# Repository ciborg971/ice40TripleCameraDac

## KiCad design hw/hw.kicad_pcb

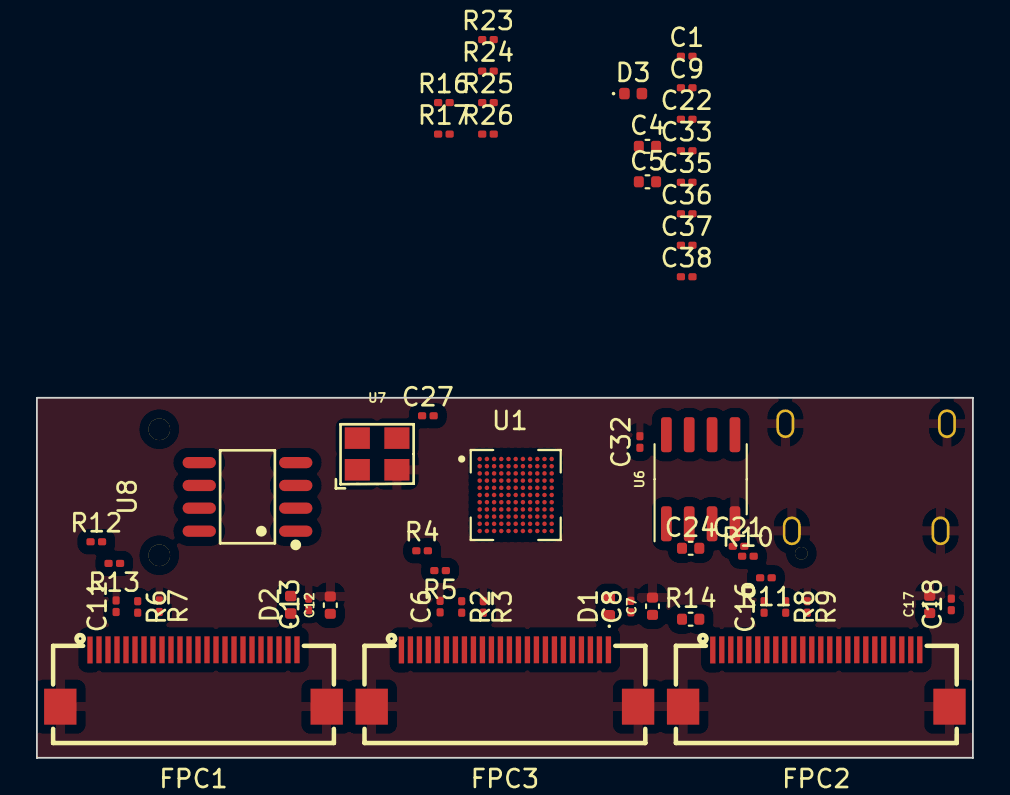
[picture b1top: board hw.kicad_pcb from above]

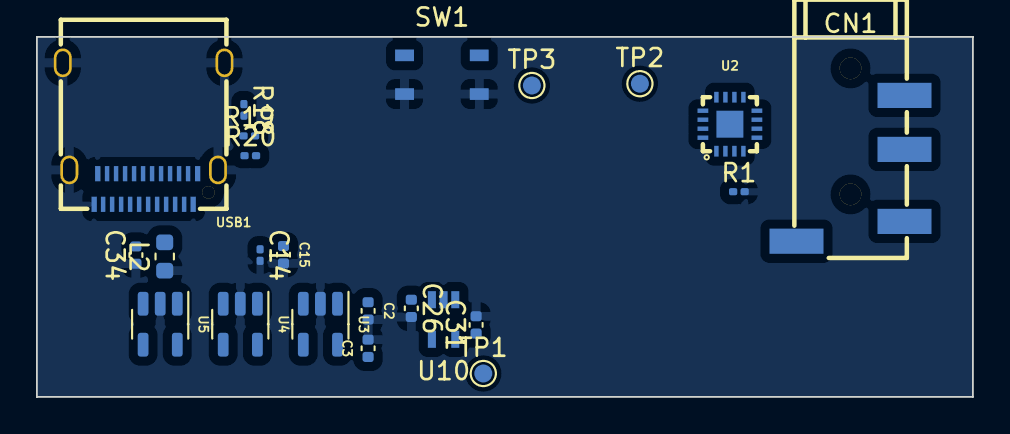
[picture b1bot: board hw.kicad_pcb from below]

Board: 2 copper layers, 52.0 x 20.0 mm, 75 parts (23 on the bottom side), 76 nets, no tracks yet.

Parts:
C1, C6, C8, C9, C11, C13, C14, C16, C18, C21, C22, C27, C32, C38: 100nF; C_0201_0603Metric
C2, C3, C4, C5: 22uF; C_0402_1005Metric
C7, C12, C17: 2.2uF; C_0402_1005Metric
C15: 4.7uF; C_0402_1005Metric
C24, C34: 10uF; C_0402_1005Metric
C26, C31: 1uF; C_0402_1005Metric
C33, C35, C36, C37: 10nF; C_0201_0603Metric
CN1: PJ-320D; AUDIO-SMD_PJ-320D
D1, D2, D3: D; D_0402_1005Metric
FPC1, FPC2, FPC3: AFC24-S24FIC-00; FPC-SMD_P0.50-24P_QCHF-SM-H2.0
L2: Bead; L_0603_1608Metric
R1, R16: 5.1K; R_0201_0603Metric
R2, R3, R6, R7, R8, R9: 10K; R_0201_0603Metric
R4, R5, R10, R11, R12, R13: 4.7K; R_0201_0603Metric
R14: 0R; C_0402_1005Metric
R17: 100; R_0201_0603Metric
R18: 1.5k; R_0201_0603Metric
R19, R20: 68; R_0201_0603Metric
R23, R24, R26: 10k; R_0201_0603Metric
R25: R; R_0201_0603Metric
SW1: SW_Push; PTS_810_SMT_Switch
TP1, TP2, TP3: TEST; TestPoint_Pad_D1.0mm
U1: ICE40LP8K-CM121; BGA121N40P11X11_500X500X100N
U2: MAX98357AETE+T; TQFN-16_L3.0-W3.0-P0.50-BL-EP1.5
U3: AP2112K-3.3; SOT-23-5
U4: AP2112K-1.8; SOT-23-5
U5: MIC5219-2.8YM5; SOT-23-5
U6: AT25SF081-SSHD-X; SOIC-8_3.9x4.9mm_P1.27mm
U7: YF4016M00033T8188092; OSC-SMD_4P-L3.2-W2.5-BL
U8: PM004MNIATR; SOP-8_L4.9-W3.9-P1.27-LS6.0-BL
U10: MIC5365-1.2YC5-TR; SC-70-C5
USB1: 12401832E402A; USB-C-TH_12401832E402A

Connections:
82: R23.2, TP2.1, U1.K6 (IOB_82_GBIN4), U6.3 (~WP/IO2)
109: R24.2, U1.H10 (IOR_116), U6.7 (~HOLD/IO3)
+1V2: C22.1, C31.1, C33.1, C35.1, R17.2, TP1.1, U1.D4 (VCC), U1.D8 (VCC__1), U1.G1 (IOL_14A_GBIN6), U1.H4 (VCC__2), U1.H8 (VCC__3), U10.5 (VOUT)
+1V8: FPC1.10, FPC2.10, FPC3.10, U4.5 (VOUT)
+2V8: D1.2 (A), D2.2 (A), D3.2 (A), FPC1.11, FPC2.11, FPC3.11, R4.2, R5.2, R10.2, R11.2, R12.2, R13.2, U5.5 (OUT)
+3.3V: C1.1, C3.1, C9.1, C14.1, C15.1, C36.1, C37.1, C38.1, R2.1, R6.1, R8.1, R23.1, R24.1, U3.5 (VOUT), U6.8 (VCC)
+3V3: C21.1, C26.1, C32.1, R14.1, R25.1, R26.1, U1.B8 (IOT_177), U1.C10 (VPP_2V5), U1.D6 (VCCIO_0), U1.E4 (VCCIO_3), U1.F8 (VCCIO_1), U1.G4 (VCCIO_3__1), U1.G10 (IOR_120), U1.H6 (VCCIO_2), U1.L11 (VCC_SPI), U7.4 (Vdd), U10.1 (VIN), U10.3 (EN)
/AVCC: FPC1.4, FPC2.4, FPC3.4
/DVP0_HREF: FPC3.9, U1.H1 (IOL_18A)
/DVP0_MCLK: FPC3.13, U1.A3 (IOT_223)
/DVP0_PCLK: FPC3.17, U1.F4 (IOL_13A)
/DVP0_SCL: FPC3.5, R5.1, U1.D10 (IOR_154)
/DVP0_SDA: FPC3.3, R4.1, U1.D11 (IOR_152)
/DVP0_VSYNC: FPC3.7, U1.H3 (IOL_17B)
/DVP0_Y2: FPC3.19, U1.J1 (IOL_23A)
/DVP0_Y3: FPC3.21, U1.K2 (IOL_25A)
/DVP0_Y4: FPC3.22, U1.J2 (IOL_25B)
/DVP0_Y5: FPC3.20, U1.K1 (IOL_23B)
/DVP0_Y6: FPC3.18, U1.H2 (IOL_18B)
/DVP0_Y7: FPC3.16, U1.F2 (IOL_12B)
/DVP0_Y8: FPC3.14, U1.A1 (IOT_225)
/DVP0_Y9: FPC3.12, U1.L4 (IOB_72)
/DVP1_HREF: FPC1.9, U1.D7 (IOT_181)
/DVP1_MCLK: FPC1.13, U1.D5 (IOT_212)
/DVP1_PCLK: FPC1.17, U1.L1 (IOB_56)
/DVP1_SCL: FPC1.5, R13.1, U1.E11 (IOR_148)
/DVP1_SDA: FPC1.3, R12.1, U1.D9 (IOR_147)
/DVP1_VSYNC: FPC1.7, U1.A5 (IOT_207)
/DVP1_Y2: FPC1.19, U1.K3 (IOB_63)
/DVP1_Y3: FPC1.21, U1.L3 (IOB_71)
/DVP1_Y4: FPC1.22, U1.G3 (IOL_17A)
/DVP1_Y5: FPC1.20, U1.J4 (IOB_64)
/DVP1_Y6: FPC1.18, U1.L2 (IOB_61)
/DVP1_Y7: FPC1.16, U1.J3 (IOB_57)
/DVP1_Y8: FPC1.14, U1.B4 (IOT_219)
/DVP1_Y9: FPC1.12, U1.A8 (IOT_190)
/DVP2_MCLK: FPC2.13, U1.B11 (IOR_161)
/DVP2_PCLK: FPC2.17, U1.A6 (IOT_206)
/DVP2_SCL: FPC2.5, R11.1, U1.E8 (IOR_146)
/DVP2_SDA: FPC2.3, R10.1, U1.E9 (IOR_144)
/DVP2_VSYNC: FPC2.7, U1.C11 (IOR_160)
/DVP2_Y2: FPC2.19, U1.A2 (IOT_222)
/DVP2_Y3: FPC2.21, U1.B3 (IOT_221)
/DVP2_Y4: FPC2.22, U1.A7 (IOT_192)
/DVP2_Y5: FPC2.20, U1.C7 (IOT_191)
/DVP2_Y6: FPC2.18, U1.H11 (IOR_119)
/DVP2_Y7: FPC2.16, U1.F1 (IOL_12A)
/DVP2_Y8: FPC2.14, U1.G8 (IOR_118)
/DVP2_Y9: FPC2.12, U1.J10 (IOR_117)
/USB_D_N: R20.2, USB1.A7 (D-), USB1.B7 (D-)
/USB_D_P: R18.1, R19.2, USB1.A6 (D+), USB1.B6 (D+)
CLK: U1.B2 (IOL_2B), U7.3 (Output)
CRESET_B: R25.2, SW1.2, TP3.1, U1.L9 (~CRESET)
GND: C1.2, C2.2, C3.2, C4.2, C5.2, C6.2, C7.2, C8.2, C9.2, C11.2, C12.2, C13.2, C14.2, C15.2, C16.2, C17.2, C18.2, C21.2, C22.2, C26.2, C31.2, C32.2, C33.2, C34.1, C35.2, C36.2, C37.2, C38.2, FPC1.2, FPC1.15, FPC1.23, FPC1.25, FPC1.26, FPC2.2, FPC2.15, FPC2.23, FPC2.25, FPC2.26, FPC3.2, FPC3.15, FPC3.23, FPC3.25, FPC3.26, L2.1, R1.2, R3.1, R7.1, R9.1, R16.2, SW1.1, U1.B1 (IOL_2A), U1.B9 (IOT_174), U1.E5 (GND), U1.E6 (GND__1), U1.E7 (GND__2), U1.F5 (GND__3), U1.F6 (GND__4), U1.F7 (GND__5), U1.G2 (IOL_14B), U1.G5 (GND__6), U1.G6 (GND__7), U1.G7 (GND__8), U1.H5 (GND__9), U3.2 (GND), U4.2 (GND), U5.2 (GND), U6.4 (GND), U7.2 (Gnd), U10.2 (GND), USB1.0, USB1.A1 (GND), USB1.A12 (GND), USB1.B1 (GND), USB1.B12 (GND)
unnamed: C6.1, FPC3.6, R2.2
unnamed: C11.1, FPC1.6, R6.2
unnamed: C16.1, FPC2.6, R8.2
unnamed: C7.1, C8.1, D1.1 (K), FPC3.24
unnamed: C12.1, C13.1, D2.1 (K), FPC1.24
unnamed: C17.1, C18.1, D3.1 (K), FPC2.24
unnamed: FPC1.8, R7.2
unnamed: FPC2.8, R9.2
unnamed: FPC3.8, R3.2
unnamed: C24.2, C27.2, U1.C5 (GNDPLL1), U1.L6 (GNDPLL0)
unnamed: C24.1, C27.1, R17.1, U1.C6 (VCCPLL1), U1.J6 (VCCPLL0)
unnamed: R14.2, U7.1 (Tri-state)
unnamed: R16.1, USB1.A5 (CC1)
unnamed: R1.1, USB1.B5 (CC2)
SCK: U1.J11 (IOR_114), U1.L10 (IOB_107_SCK), U6.6 (SCK)
SDI: U1.J9 (IOB_106_SDI), U6.2 (SO/IO1)
SDO: U1.H9 (IOB_104_CBSEL1), U1.K9 (IOB_105_SDO), U6.5 (SI/IO0)
SS: R26.2, U1.K10 (IOB_108_SS), U1.K11 (IOR_115), U6.1 (~CS)
USB_N: R20.1, U1.B5 (IOT_208)
USB_P: R19.1, U1.A4 (IOT_211)
USB_PU: R18.2, U1.A9 (IOT_178)
VBUS: C2.1, C4.1, C5.1, C34.2, L2.2, U3.1 (VIN), U3.3 (EN), U4.1 (VIN), U4.3 (EN), U5.1 (IN), U5.3 (EN), USB1.A4 (VBUS), USB1.A9 (VBUS), USB1.B4 (VBUS), USB1.B9 (VBUS)

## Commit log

2024-01-02 unfinished schematic
2024-01-03 switch to a fpga with more gpio + doc
